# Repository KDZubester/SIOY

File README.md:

# Instructions for Downloading and Setting Up Arduino Program and GitHub Files
Hello future engineers! We are excited to share this fun engineering project with you! These instructions will guide you on your first steps to changing the world with your skills and ideas. In preparation to create your own DIY Digital Watch, you will learn how to set up the coding environment you will use to control an Arduino and how to get your first program to run. There are three main sections to these instructions: (1) downloading the Arduino program; (2) downloading the GitHub files; (3) compiling the Arduino code needed to begin the DIY Digital Watch project. This process should take no more than 20 minutes. So let's get started!

## Materials required:
These instructions are meant for **WINDOWS 11** computers. If you are using a Linux or Mac, the user interface will look different.

## Downloading the Arduino Program

### Step 1
Go to this webpage: https://www.arduino.cc/en/software

### Step 2
Click on one of these three links to start the download. The link you need to click on will change depending on what type of computer you are using. **Note:** It will ask you if you want to donate money before downloading the Arduino program. You DON'T need to do this. You can just download the program if you want.

### Step 3
Click the file once the download is complete to launch the installer.

### Step 4
Agree to Terms and Conditions 

### Step 5
Choose to install for a single user

### Step 6
Accept default file location. But you can pick a location that better suits you if you want.

### Step 7
Complete installation and open the Arduino IDE

## Downloading the GitHub files

### Step 8
Open the GitHub repository and click on green button that says "Code"

### Step 9
Click "Download Zip" from the dropdown menu that appeared. This will download a .zip file that contains all of the folders you will need for this project

### Step 10
Click the carrot symbol on the icon that appeared on the bottom left of your window.

### Step 11
Choose the "Show in Folder" option.

Clicking on that option will take you to the location where that .zip folder was downloaded to. You can change the location of this folder so it is easier to find later.

### Step 12
Right click on the folder to make an options menu appear.

### Step 13
Select "Extract All". This will allow you to fully access the data inside of the .zip folder

### Step 14
Select the location for the computer to send the unzipped folder to.
If you have not already picked an easy place to find the folder for later use, please do so now. **We will need to access and change some of the files you just downloaded. So, it is very important that you know where they are!**

Once the computer is done extracting the data from the folder, it will take you inside the newly unzipped folder.

### Step 15
Double click on "Self-Starter-Kits-main" to enter the folder. There is a lot of stuff inside the folder. You can explore and use it however you want.

### Step 16
Double click on the folder titled, "Watch_02.1" This folder has all of the code that the DIY Digital Watch will need to run.

### Step 17
Double click on the file named "Watch_02.1.ino" This will open the Arduino project in the Arduino Program

## Compiling Arduino Code for the first time

### Step 18
Click Tools and then hover over the "Board" setting, then "Arduino AVR boards", then select "Arduino Nano" to select the type of board we will be using

### Step 19
Click "Tools" and then hover over the "Processor" setting, then select "ATMega328P (Old Bootloader)" to choose the processor

### Step 20
Click the Verify button (the checkmark) to compile program

Compilation errors will be reported in the output window

**NOTE:** Most users will be missing the libraries required for the watch code to run correctly. So, the compilation will most likely fail. **This is expected at this point.** We will now grab the libraries we need and put them into the Arduino program.

### Step 21
Open two File Explorer windows side-by-side 

### Step 22
Click on "This PC" in each window

### Step 23 
Type "libraries" in the search bars of both windows. 

Then select "libraries - Arduino" in one, and "libraries - Self-Starter-Kits-main" in the other

This is what you should see in the two windows

### Step 24
Copy everything in the "libraries - Self-Starter-Kits-main" folder except the readme.txt file

### Step 25
Paste those folders into the "libraries - Arduino" folder

This is what you should now see in the two windows

### Step 26
Go back to the Arduino program and press the compile button again. The output should show all white text and give information about how many bytes the sketch uses.

If your output screen looks similar to ours then you are done. Way to go!

## What if the Arduino program still shows errors???

Do not worry if the Arduino program still won't compile. All you need to do is follow these steps to manually download the necessary libraries.

### Step 1
Open the Library Manager by clicking the book icon on the left side of the screen

Search for the missing library. The word you need to search is in the output terminal. Our example says "#include "U8glib.h," so the library we need to search for is "U8glib."

Choose the library you are looking for and click "Install"
**NOTE:** If the install button is not visible, expand the Library Manager window
**NOTE:** If it is not clear which library to install, googling the .h file that throws an error will be helpful

If you have other questions, feel free to email us at daniel@zubeldia.us for more help

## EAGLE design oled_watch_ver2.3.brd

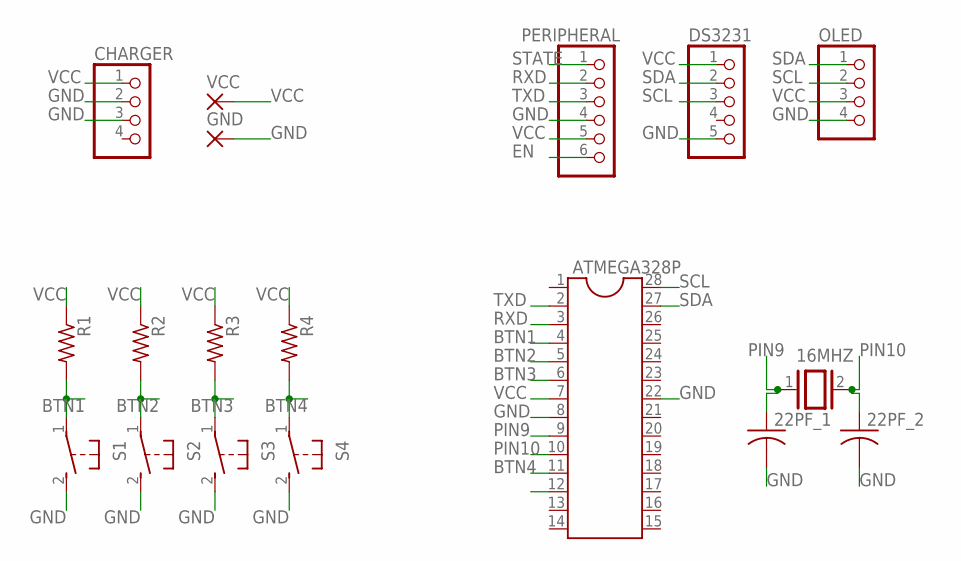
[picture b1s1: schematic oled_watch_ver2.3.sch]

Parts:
16MHZ: XTAL/S; QS
22PF_1, 22PF_2: C-US025-024X044; C025-024X044
ATMEGA328P: DIL28-3
CHARGER: PINHD-1X4; 1X04
DS3231: PINHD-1X5; 1X05
GND: 2,54/0,8
OLED: PINHD-1X4; 1X04
PERIPHERAL: PINHD-1X6; 1X06
R1, R2, R3, R4: R-US_0207/7; 0207/7
S1, S2, S3, S4: 31-XX; B3F-31XX
VCC: 2,54/0,8

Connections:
BTN1: ATMEGA328P.4, R1.2, S1.1
BTN2: ATMEGA328P.5, R2.2, S2.1
BTN3: ATMEGA328P.6, R3.2, S3.1
BTN4: ATMEGA328P.11, R4.2, S4.1
EN: PERIPHERAL.6
GND: 22PF_1.2, 22PF_2.2, ATMEGA328P.8, ATMEGA328P.22, CHARGER.2, CHARGER.3, DS3231.5, GND.1, OLED.4, PERIPHERAL.4, S1.2 (S), S2.2 (S), S3.2 (S), S4.2 (S)
LED: ATMEGA328P.12
PIN9: 16MHZ.1, 22PF_1.1, ATMEGA328P.9
PIN10: 16MHZ.2, 22PF_2.1, ATMEGA328P.10
RXD: ATMEGA328P.3, PERIPHERAL.2
SCL: ATMEGA328P.28, DS3231.3, OLED.2
SDA: ATMEGA328P.27, DS3231.2, OLED.1
STATE: PERIPHERAL.1
TXD: ATMEGA328P.2, PERIPHERAL.3
VCC: ATMEGA328P.7, CHARGER.1, DS3231.1, OLED.3, PERIPHERAL.5, R1.1, R2.1, R3.1, R4.1, VCC.1

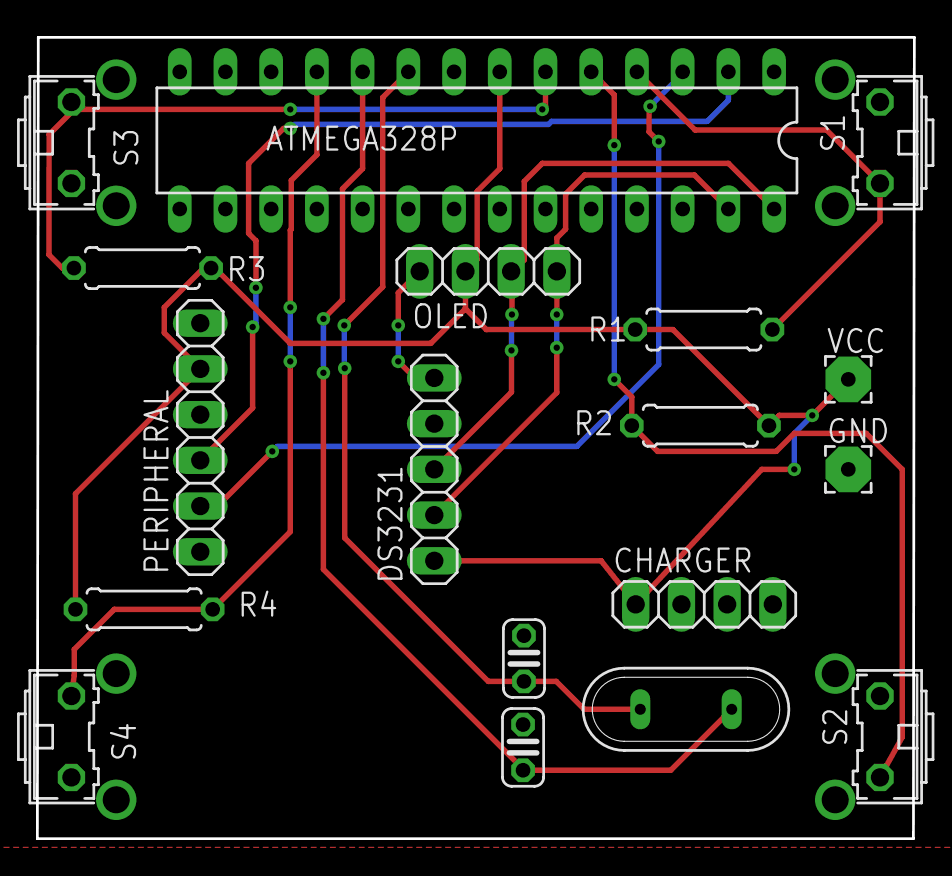
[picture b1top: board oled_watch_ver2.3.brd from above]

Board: 2 copper layers, 48.7 x 44.5 mm, 18 parts (0 on the bottom side), 12 nets.

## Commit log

2023-01-24 Took out Battery number display
2023-02-02 Added most recent eagle files
2023-02-03 Added step files of PCB
2023-02-03 Uploaded svg file for acrylic screen protector
2023-02-07 Included Case STL Files
